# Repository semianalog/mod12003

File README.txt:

MOD12003  [[WIP]]
=================

Work in progress.

20V 3A power supply module for MOD1 series of modular power supplies.

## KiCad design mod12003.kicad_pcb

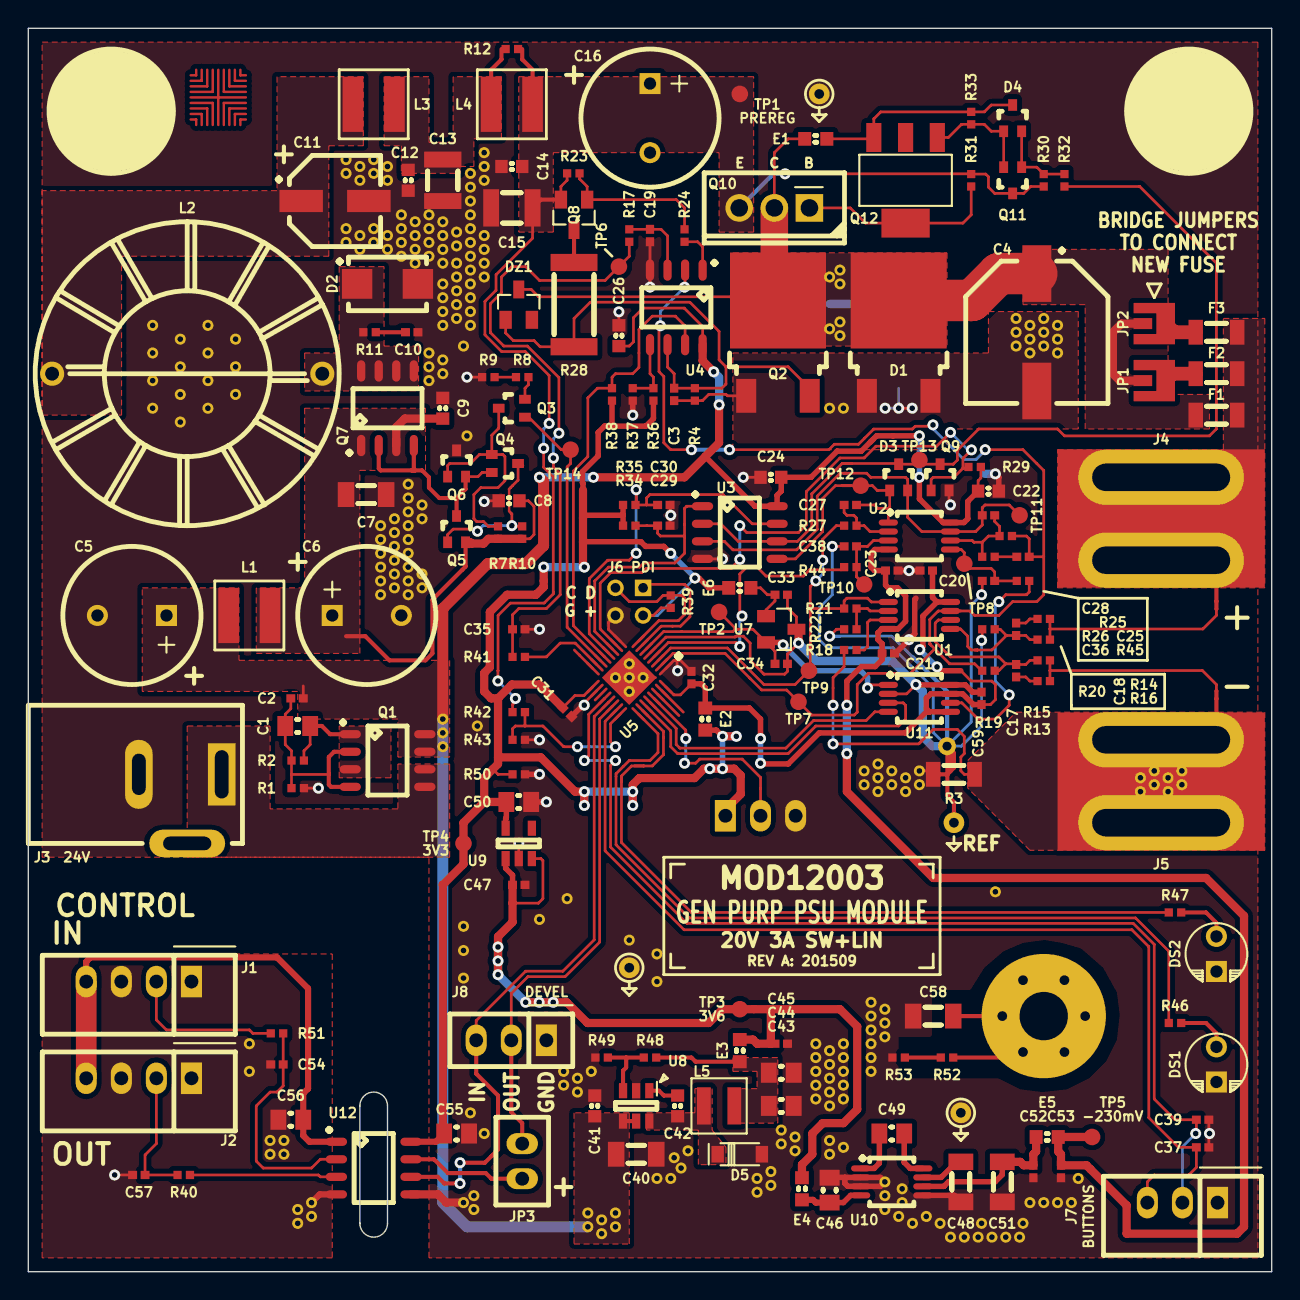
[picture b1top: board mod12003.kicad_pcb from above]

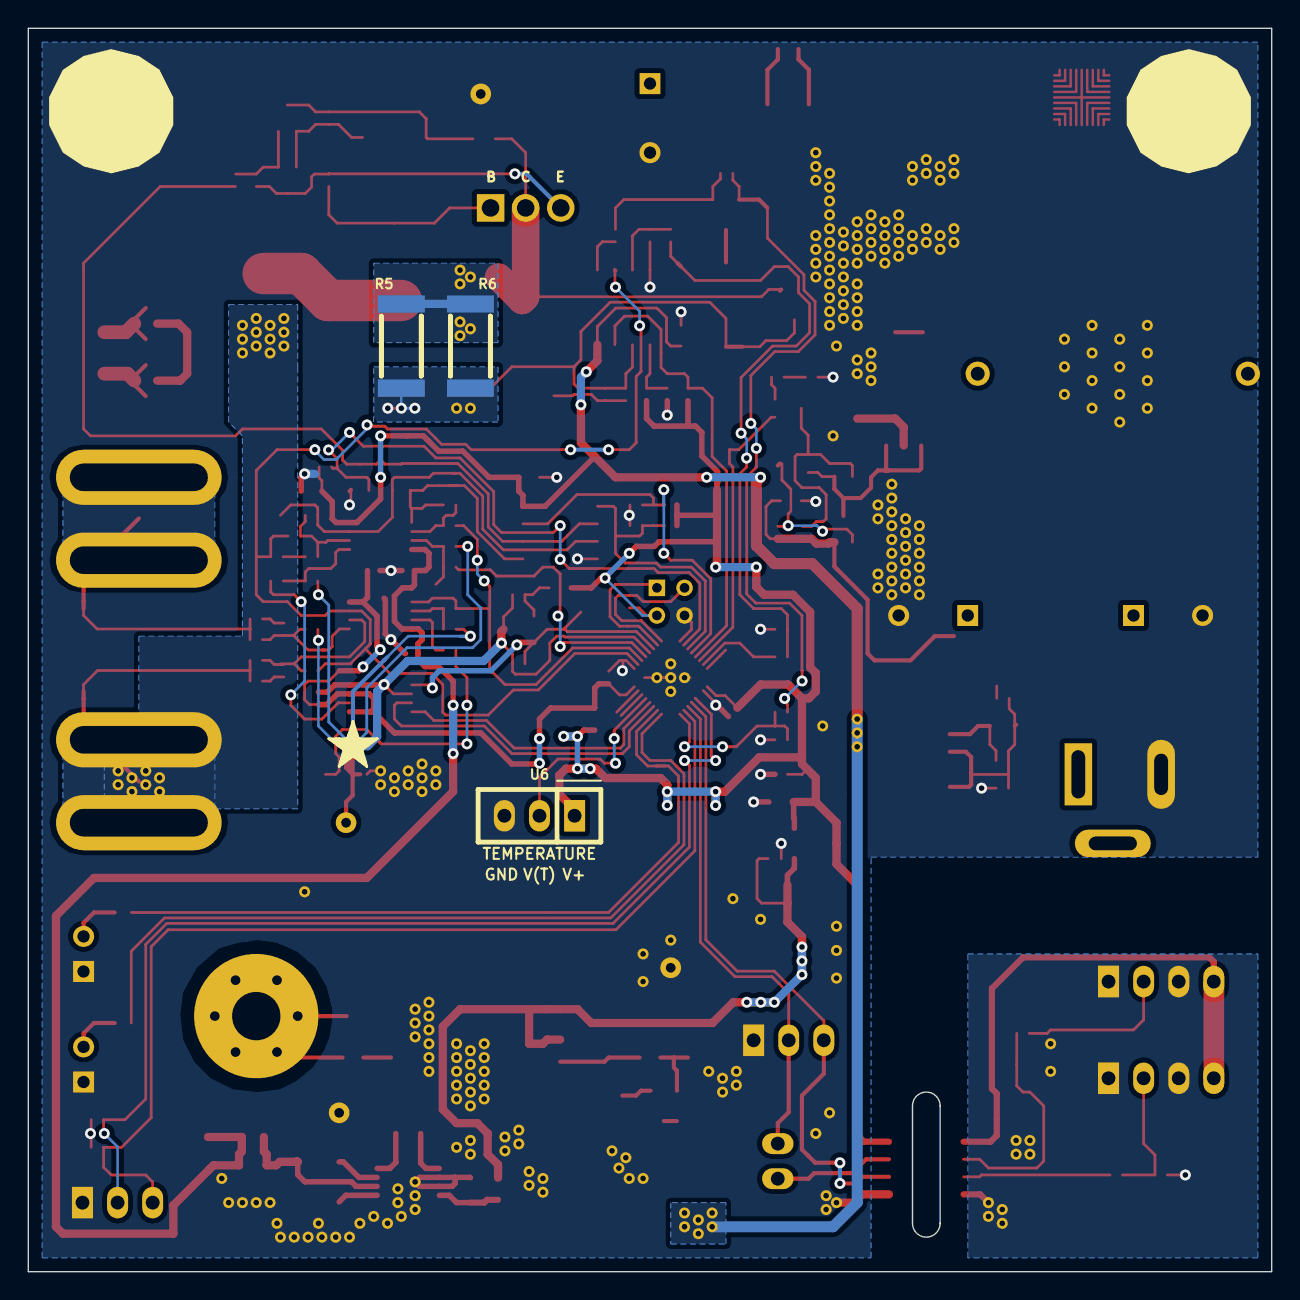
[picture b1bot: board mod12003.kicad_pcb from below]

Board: 2 copper layers, 90.0 x 90.0 mm, 281 parts (3 on the bottom side), 97 nets.

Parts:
C1, C55, C56: 1u; CAPC2012X70
C2, C17, C18, C25, C27, C29, C30: 22n; CAPC1005X55
C3, C19, C20, C21, C23, C31, C32, C33, C34, C35, C36, C37, C38, C39, C45, C47, C52, C53, C59: 100n; CAPC1005X55
C4: 330u; CAPAE1030X1250
C5, C6, C16: 470u; C-ALUM-10mm
C7, C40: 6u8; CAPC3216X70
C8, C9, C12, C14, C22, C24, C26, C41, C42: 100n; CAPC1608X55
C10, C28, C54, C57: 220p; CAPC1005X55
C11: 33u; CAPAE660X570
C13, C15: 1u; CAPC3225X88
C43, C44, C46, C49, C50: 4u7; CAPC2012X70
C48, C51: 22u; CAPC3216X70
C58: 1k/1kV; CAPC3216X70
D1: 40V/5A; TO-252
D2: MBRS360B; DIOM5436X244
D3, D4: BAT54AWT; SC-70
D5: MBR0530; SOD-123
DS1: CC; LED-5mm
DS2: CV; LED-5mm
DZ1: 84B24; SOT-23
E1, E2, E3, E4, E5, E6: 120; INDC1608X95
F1, F2, F3: 4A; RESC3216X60
J1: IN; CONN-100MIL-M-1x4-SHROUD
J2: OUT; CONN-100MIL-M-1x4-SHROUD
J3: 24V; CONN-PJ-037A
J4: OUT+; J1
J5: OUT-; J1
J6: PDI; CONN-100MIL-M-2x3
J7: BUTTONS; CONN-100MIL-M-1x3-SHROUD
J8: DEVEL; CONN-100MIL-M-1x3
JP1, JP2: JUMPER-SOLDER; JUMPER-SOLDER-3mm
JP3: JUMPER; CONN-100MIL-M-1x2
L1, L3, L4: 3u3; BOURNS-SRN5040
L2: 100u; L1
L5: 22u; BOURNS-SRN3015
MP1, MP2, MP3: SCREW; SCREW-4-SUPPORTED
Q1, Q7: AO4805; SOIC127P600X175-8
Q2: 12A; TO-252
Q3, Q4: 3904; SC-70
Q5, Q6: 4403; SC-70
Q8: 4403; SOT-23
Q9: 2N7002PW; SC-70
Q10: D45H11; TO-220
Q11: PMSS3904; SC-70
Q12: PZT3904; SOT-223
R1, R2, R34, R35, R38, R41, R52, R53: 470k; RESC1005X40
R3: R010; RESC3216X60
R4, R22, R32, R37, R44, R45: 348; RESC1005X40
R5, R6, R28: 1k; RESC6432X70
R7, R15, R16, R21, R23, R24, R25, R29, R30, R39, R42: 22k; RESC1005X40
R8, R9, R10, R13, R14, R17, R18, R19, R20, R26, R27, R31, R33, R36, R43, R46, R47, R49, R50: 2k; RESC1005X40
R11, R12, R40, R51: 100; RESC1005X40
R48: 6k98; RESC1005X40
TP1: PREREG; TEST-SMD-SMALL
TP2: 2V048; TEST-SMD-SMALL
TP3: 3V6; TEST-SMD-SMALL
TP4: 3V3; TEST-SMD-SMALL
TP5: -230mV; TEST-SMD-SMALL
TP6: OVP_TH; TEST-SMD-SMALL
TP7: VSENSE; TEST-SMD-SMALL
TP8: VSET; TEST-SMD-SMALL
TP9: ISENSE; TEST-SMD-SMALL
TP10: ISET; TEST-SMD-SMALL
TP11: VDRIVE; TEST-SMD-SMALL
TP12: IDRIVE; TEST-SMD-SMALL
TP13: DRIVE; TEST-SMD-SMALL
TP14: SW; TEST-SMD-SMALL
U1: OPA2376AIDGK; SOP65P490X110-8
U2: LM358DGK; SOP65P490X110-8
U3, U4: LM393M; SOIC127P600X175-8
U5: ATXMEGA32E5-M4U; QFN40P400X400X55-33
U6: MCP9701-E/TO; CONN-100MIL-M-1x3
U7: ADR380; SOT-23
U8: AOZ1282; SOT-23-6
U9: TLV70233DBV; SOT-23-5
U10: LM7705; SOP65P490X110-8
U11: MAX5215; SOP65P490X110-8
U12: Si8421; SOIC127P600X175-8
VIA5, VIA5#2, VIA5#3, VIA5#4, VIA5#5, VIA5#6, VIA11, VIA12, VIA21, VIA22, VIA32, VIA311, VIA312, VIA321, VIA322, VIA331, VIA331#2, VIA331#3, VIA3111, VIA3111#2, VIA3111#3, VIA3112, VIA3112#2, VIA3112#3, VIA3112#4, VIA3112#5, VIA3112#6, VIA3112#7, VIA3112#8, VIA3112#9, VIA3112#10, VIA3112#11, VIA3112#12, VIA3112#13, VIA3112#14, VIA3112#15, VIA3112#16, VIA3112#17, VIA3121, VIA3121#2, VIA3122, VIA3122#2, VIA3311, VIA3312, VIA3313, VIA3321, VIA3322, VIA3323, VIA3331, VIA3332, VIA3333, VIA33111, VIA33112, VIA33113, VIA33114, VIA33115, VIA33121, VIA33122, VIA33123, VIA33124, VIA33125, VIA33131, VIA33132, VIA33133, VIA33134, VIA33135, VIA33211, VIA33212, VIA33212#2, VIA33212#3, VIA33212#4, VIA33212#5, VIA33221, VIA33222, VIA33223, VIA33231, VIA33232, VIA33233, VIA33241, VIA33242, VIA33243, VIA331111, VIA331112, VIA331311, VIA331312, VIA331313, VIA331321, VIA331322, VIA331323, VIA331331, VIA331332, VIA331333: VIA-0.8mm
W1, W2, W3: NET-TIE; NET-TIE-0.3mm

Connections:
+3.3: C31.1, C50.1, C55.1, E2.1, E6.1, J6.2, R34.2, R35.2, R36.2, R38.2, R39.2, R50.1, TP4.1, U5.17, U6.1, U9.5, U12.8
+3.3A: C20.1, C32.1, C59.1, E2.2, U1.8, U5.32, U11.5, U11.7
+3.6: C45.1, C47.1, E3.2, E4.1, TP3.1, U9.1, U9.3
/Control/BTN1: C39.1, J7.2, U5.20
/Control/BTN2: C37.1, J7.3, U5.23
/Control/ISENSE: R21.2, R27.2, TP9.1, U1.1, U5.3
/Control/ISET: C38.1, R44.1, TP10.1, U2.3
/Control/LEDCC: R46.1, U5.25
/Control/LEDCV: R47.1, U5.26
/Control/OVPTH_PWM: R41.2, U5.15
/Control/OVP_THRESH: C35.1, R17.2, R41.1, TP6.1
/Control/PDI_C: J6.5, R39.1, U5.8
/Control/PDI_D: J6.1, U5.7
/Control/PREREG_SW: Q3.1, TP14.1, U5.14
/Control/RX: J8.2, JP3.2, U5.22
/Control/SCL: U5.27, U11.3
/Control/SDA: U5.28, U11.4
/Control/TEMP: U5.29, U6.2
/Control/VREF: C34.1, TP2.1, U5.6, U7.2, U11.1
/Control/VSENSE: C25.2, R19.1, R25.2, TP7.1, U1.7, U4.2, U5.2
/Control/VSET: C36.1, R45.1, TP8.1, U2.5
/Control/~EN: Q9.1, R29.1, U5.10
/Control/~ILIM: C30.2, R35.1, U3.7, U5.12
/Control/~SCR_TRIPPED: R38.1, U4.7, U5.13
/Control/~VLIM: C29.2, R34.1, U3.1, U5.11
/Iso/FROM_ISO_IN: JP3.1, U12.7
/Iso/ISO_5V: C56.1, J1.4, J2.4, U12.1
/Iso/ISO_GND: C54.1, C56.2, C57.1, J1.1, J1.3, J2.1, J2.3, U12.4, VIA3112.1, VIA3112#2.1, VIA3112#3.1, VIA3112#4.1, VIA3112#5.1, VIA3112#6.1, VIA3112#7.1, VIA3112#8.1, VIA3112#9.1, VIA3112#10.1
/Iso/ISO_IN: J1.2, R51.2
/Iso/ISO_OUT: C57.2, J2.2, R40.2
/Iso/TO_ISO_OUT: J8.3, U5.21, U12.6
/Linear/ISENSE: C3.2, C4.2, D1.A, J5.1, Q2.K, R3.1, R4.1, R5.1, R6.1, R18.2, W3.2
/Linear/P_IN: C14.2, C15.1, C16.1, L4.1, Q8.2, Q10.3, Q11.3, R12.1, R23.2, R30.2, R31.2, R42.1, TP1.1
/Linear/P_OUT: C4.1, D1.K, DZ1.3, E1.1, F1.2, JP1.1, JP2.1, Q2.A, Q10.2, R5.2, R6.2, VIA5.1, VIA5#2.1, VIA5#3.1, VIA5#4.1, VIA5#5.1, VIA5#6.1
/Linear/SCR_FIRE: C3.1, DZ1.1, Q2.G, R4.2, R28.1, U4.6
/Linear/VSENSE+: R14.2, R16.2, W2.1
/Linear/VSENSE-: R13.2, R15.2, W3.1
/LocalPwr/3V6SW: C42.2, D5.1, L5.2, U8.6
/LocalPwr/3V6UF: C43.1, C44.1, E3.1, L5.1, R48.1
/LocalPwr/3V6_7705: C46.1, E4.2, U10.4
/LocalPwr/CF+: C49.2, U10.1
/LocalPwr/CF-: C49.1, U10.8
/OUT+: F1.1, F2.1, F3.1, J4.1, W2.2
/PAD_MP1: C58.1, MP1.1, R52.2
/Preregulator/PREF1: C11.1, L2.1, L3.2
/Preregulator/PREF2: C12.2, C13.1, L3.1, L4.2, R12.2
/Preregulator/SWNODE: D2.1, L2.2, Q7.5, Q7.6, Q7.7, Q7.8, R11.2
/Preregulator/V+F: C6.1, C7.1, C8.2, C9.2, L1.1, Q5.2, Q7.1, Q7.3, R7.1, R10.1
/VIN: J3.1, Q1.5, Q1.6
/VRP: C1.1, Q1.1, Q1.3, R2.2
GND: C5.2, C6.2, C7.2, C8.1, C9.1, C10.1, C11.2, C12.1, C13.2, C14.1, C15.2, C16.2, C19.2, C20.2, C21.2, C22.1, C23.2, C24.1, C26.1, C29.1, C30.1, C31.2, C32.2, C35.2, C37.2, C39.2, C40.2, C41.2, C43.2, C44.2, C45.2, C46.2, C47.2, C48.2, C50.2, C51.2, C52.2, C53.2, C55.2, C58.2, D2.2, D5.2, DS1.1, DS2.1, J3.2, J6.6, J7.1, J8.1, Q6.3, Q9.2, R1.1, R3.2, R9.2, R37.1, R43.2, R49.2, R50.2, R53.1, U3.4, U4.4, U5.1, U5.9, U5.18, U5.33, U6.3, U8.2, U9.2, U10.2, U10.3, U10.5, U12.5, VIA11.1, VIA12.1, VIA21.1, VIA22.1, VIA32.1, VIA311.1, VIA312.1, VIA321.1, VIA322.1, VIA331.1, VIA331#2.1, VIA331#3.1, VIA3111.1, VIA3111#2.1, VIA3111#3.1, VIA3112#11.1, VIA3112#12.1, VIA3112#13.1, VIA3112#14.1, VIA3112#15.1, VIA3112#16.1, VIA3112#17.1, VIA3121.1, VIA3121#2.1, VIA3122.1, VIA3122#2.1, VIA3311.1, VIA3312.1, VIA3313.1, VIA3321.1, VIA3322.1, VIA3323.1, VIA3331.1, VIA3332.1, VIA3333.1, VIA33111.1, VIA33112.1, VIA33113.1, VIA33114.1, VIA33115.1, VIA33121.1, VIA33122.1, VIA33123.1, VIA33124.1, VIA33125.1, VIA33131.1, VIA33132.1, VIA33133.1, VIA33134.1, VIA33135.1, VIA33211.1, VIA33212#2.1, VIA33212#3.1, VIA33212#4.1, VIA33212#5.1, VIA33221.1, VIA33222.1, VIA33223.1, VIA33231.1, VIA33232.1, VIA33233.1, VIA33241.1, VIA33242.1, VIA33243.1, VIA331111.1, VIA331112.1, VIA331311.1, VIA331312.1, VIA331313.1, VIA331321.1, VIA331322.1, VIA331323.1, VIA331331.1, VIA331332.1, VIA331333.1, W1.1
unnamed: C1.2, C2.2, Q1.2, Q1.4, R1.2, R2.1
unnamed: C10.2, R11.1
unnamed: C17.1, R15.1, R19.2, U1.6
unnamed: C17.2, R13.1
unnamed: C18.1, R16.1, R20.2, U1.5
unnamed: C18.2, R14.1
unnamed: C19.1, R17.1, U4.3
unnamed: C25.1, R26.2
unnamed: C27.1, D3.1, TP12.1, U2.1, U3.5
unnamed: C27.2, R27.1, U2.2
unnamed: C28.1, D3.2, TP11.1, U2.7, U3.3
unnamed: C28.2, R25.1, R26.1, U2.6
unnamed: C33.1, E6.2, U7.1
unnamed: C42.1, U8.1
unnamed: C48.1, U10.7
unnamed: C51.1, C52.1, E5.1, U10.6
unnamed: C54.2, R51.1, U12.2
unnamed: D3.3, Q9.3, R32.1, TP13.1, U3.2, U3.6
unnamed: D4.1, Q11.2, Q12.1, R33.2
unnamed: D4.2, Q11.1, R30.1, R32.2
unnamed: D4.3, E1.2, Q12.3, R33.1
unnamed: DS1.2, R46.2
unnamed: DS2.2, R47.2
unnamed: F2.2, JP1.2
unnamed: F3.2, JP2.2
unnamed: Q3.2, R8.1
unnamed: Q3.3, Q4.1, Q6.1, R7.2
unnamed: Q4.2, Q5.3, Q6.2, Q7.2, Q7.4
unnamed: Q4.3, Q5.1, R10.2
unnamed: Q8.1, R23.1, R24.2
unnamed: Q8.3, R28.2
unnamed: Q10.1, Q12.4, R31.1
unnamed: R8.2, R9.1
unnamed: R18.1, U1.3
unnamed: R21.1, R22.2, U1.2
unnamed: R24.1, U4.1
unnamed: R36.1, R37.2, U4.5
unnamed: R40.1, U12.3
unnamed: R42.2, R43.1, U5.24
unnamed: R44.2, U5.4
unnamed: R45.2, U11.6
unnamed: R48.2, R49.1, U8.3
unnamed: R52.1, R53.2
REFGND: C33.2, C34.2, C36.2, C38.2, C59.2, R20.1, R22.1, U5.5, U7.3, U11.2, U11.8, VIA33212.1, W1.2
V+: C2.1, C5.1, C22.2, C24.2, C26.2, C40.1, C41.1, L1.2, Q1.7, Q1.8, R29.2, U2.8, U3.8, U4.8, U8.4, U8.5
V-: C21.1, C23.1, C53.1, E5.2, TP5.1, U1.4, U2.4

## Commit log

2015-08-19 Add simulation
2015-08-19 First working version
2015-08-19 Reannotate component references
2015-08-29 Piles and piles of work
2015-08-29 Add documentation
2015-08-29 Rename project from modpsu to mod12003
2015-08-29 Remove OSHW logo
2015-08-29 Update docs
2015-08-29 Add license, readme
2015-08-29 Remove extra term in license
2015-08-29 Documentation editing
2015-08-30 Add some comms documentation
2015-09-21 Finish PCB
2015-09-21 Add firmware
2015-09-25 Add untested CRC
2015-09-27 Working CRC
2015-09-27 Switch to single-byte command
2015-09-27 Add loop handlers
2015-09-28 Code cleanup, begin splitting out receiver
2015-09-28 Remove unused includes
2015-09-28 Add SERIAL and COUNT commands
2015-09-29 Add bit-banged I2C master
2015-09-29 Add I2C DAC
2015-10-31 Remove old firmware
2015-11-02 Add initial new firmware
2015-11-02 Switch to C11
2015-11-02 Refactor cal code
2015-11-02 Refactor DAC control
2015-11-02 Remove remaining cli/sei
2015-11-02 Tweak optimization flags
2015-11-02 Use proper AFW Makefile
2015-11-02 Use new AFW u8/u16/u32 macros
2015-11-02 Simplify serial number
2015-11-02 Output timing signal for debug
2015-11-02 Cal routine: always finish on abort
2015-11-02 Add simple calibration
2015-11-02 Adjust calibration points for better accuracy
2015-11-02 Set PSU output voltage using calibration
2015-11-02 Remove unnecessary inlines
2015-11-02 Remove the last of PROGMEM
2015-11-02 Add voltage monitoring and reporting
2015-11-02 Add voltage control loop
2015-11-02 Remove branding from schematic (may re-add later)
2015-11-02 Kill magic numbers
2015-11-02 Optimize PSU controller a bit
2015-11-02 Reduce comm buffer size
    Stack overhead for RAM is getting worryingly low..
2015-11-03 Fix regression in prereg control
2015-11-03 Remove TODO comment
    No, resetting the accumlator cannot be skipped. Recovery time is too
    long.
2015-11-03 Set preregulator before calibration
2015-11-03 Add LEDs and mode reporting
2015-11-03 Add output enable (known bug!)
    Bug: output voltage blips to about 5.4V at enable.
2015-11-03 Fix output blip
    Add a bodge wire to prototype to allow the MCU to force the regulator
    into saturation-low
2015-11-03 Add current control
2015-11-03 Rework calibration
2015-11-03 Remove extra casts, add send_ack
2015-11-03 Fix typo in comment
2015-11-03 Add setpoint readback
2015-11-03 Add command length validation
2015-11-03 Add command range checking
2015-11-03 Replace sprintf to reduce code size
2015-11-04 Add temperature sense and debug info command
2015-11-04 Tweak control loop windup prevention
2015-11-04 Reset integrator whenever not integrating
2015-11-04 Downsize unnecessarily large integers
2015-11-04 Add test scripts
2015-11-04 Initial power dissipation measurement (buggy)
2015-11-04 Interrupt-safety fixes
2015-11-04 Use AFW Makefile's new call analysis
2015-11-04 Add helpers for call analysis
2015-11-13 Add PSRR improvement
2015-11-13 Remove comments about insulating screws
    Final PCB used insulated pads
2015-11-17 Update branding
2015-11-17 Revise schematic
2015-11-17 Update licensing
2015-11-18 memxify send_msg
2016-01-17 Sch library updates
2016-01-17 Switch programmer
2016-01-17 Fix psu_powerdis_get_10mw
2016-01-17 Add disable_regulator()
2016-01-17 Fix disable logic: only call once
2016-01-17 Only access the prereg from one routine
2016-01-17 Disable prereg when PSU is disabled
2016-01-17 Make sure preregulator starts switched off
2016-01-17 Factor out enable_or_disable()
2016-01-17 Factor out voltage_integrator_cycle()
2016-01-17 Remove VOLTAGE_LOOP_SKIPS
2016-01-18 Rearrange functions from psu.c
2016-01-18 Add KiCad libraries as submodules
2016-01-18 Update schlib
2016-01-18 Update schematic to new symbols
